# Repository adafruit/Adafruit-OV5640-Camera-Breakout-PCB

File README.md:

## Adafruit OV5640 Camera Breakout - 120 Degree Lens PCB

<a href="http://www.adafruit.com/products/5673"><br/>
Click here to purchase one from the Adafruit shop</a>

PCB files for the Adafruit OV5640 Camera Breakout - 120 Degree Lens. 

Format is EagleCAD schematic and board layout
* https://www.adafruit.com/product/5673

### Description

Hobby-level microcontrollers are finally getting big and powerful enough to start handling camera modules that historically would have required a full computer or FPGA to handle. The RP2040 and ESP32-Sx series of chips, for example, have enough pins to communicate with the 8-bit data output, DMA to quickly grab a frame, and the necessary RAM to buffer a raw snapshot. Now all we need is a nice camera module to make interfacing easy!

This Adafruit OV5640 Camera Breakout with 120 Degree Lens has a nice quality OV5640 camera with a 5 Megapixel sensor element, 120-degree wide angle lens, and all the support circuitry you need. We looked at existing camera modules and while this breakout board is backwards compatible, we made some improvements:

* Standard 2x9 header if you want it, but also a duplicated header strip 0.3" apart so you can plug it into a breadboard or perfboard 
* Selectable external or internal 24MHz "XCLK" clock generation - save one gpio pin, or just have a nice stable 24 MHz signal even if your microcontroller can't generate it for you.
* Heat-sinking camera area with exposed ground pad, with lots of vias for good thermal transfer. Helpful for when doing continuous encoding and reducing thermal image drift.
* Optional VMotor 3.3V power jumper on DATA1, for auto-focusing camera modules
* 3.3V power-good LED on back that can be disabled

### License

Adafruit invests time and resources providing this open source design, please support Adafruit and open-source hardware by purchasing products from [Adafruit](https://www.adafruit.com)!

Designed by Limor Fried/Ladyada for Adafruit Industries.

Creative Commons Attribution/Share-Alike, all text above must be included in any redistribution. 
See license.txt for additional details.

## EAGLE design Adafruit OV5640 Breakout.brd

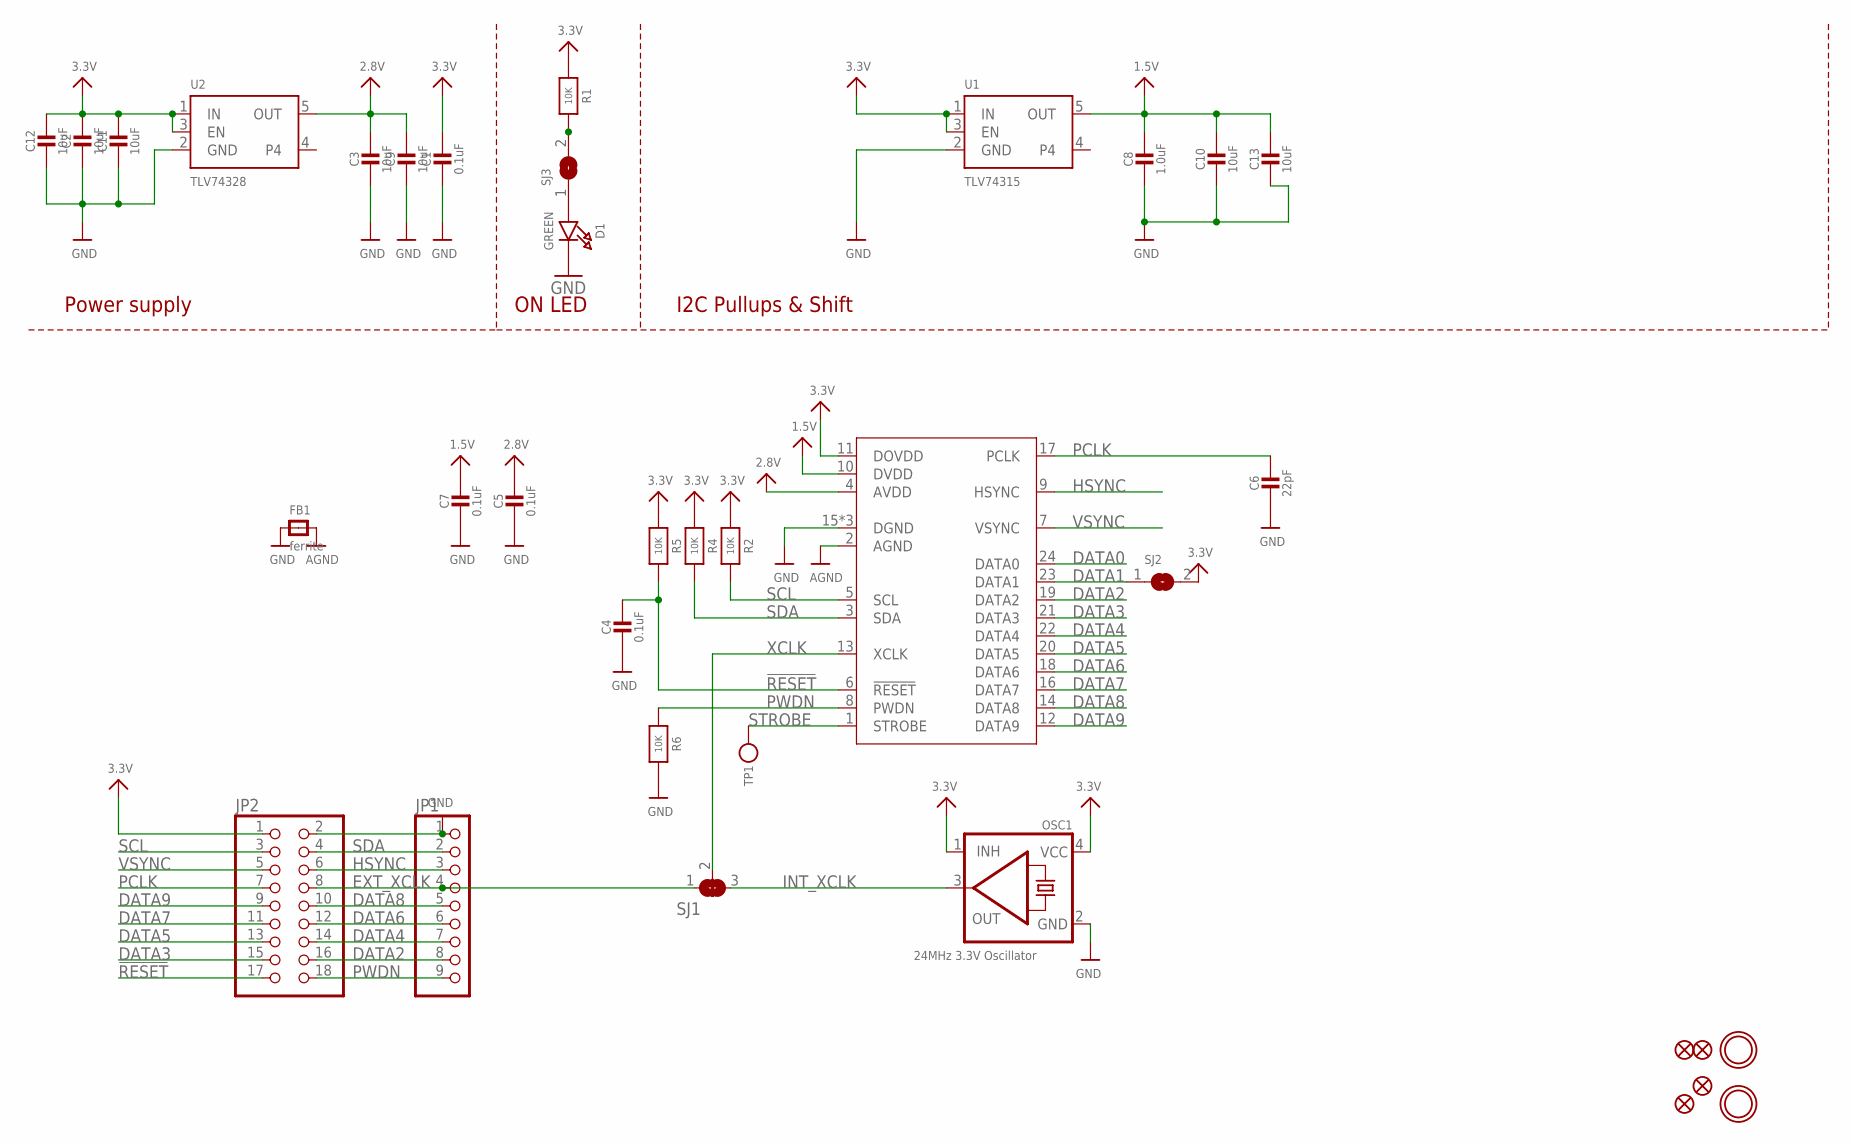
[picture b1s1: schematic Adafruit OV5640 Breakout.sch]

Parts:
C1, C4, C5, C7: 0.1uF; 0603-NO
C2, C3, C9, C10, C11, C12, C13: 10uF; 0805-NO
C6: 22pF; 0603-NO
C8: 1.0uF; 0603-NO
D1: GREEN; CHIPLED_0603_NOOUTLINE
FB1: ferrite; 0603-NO
FID1, FID2, FID3, FID4: FIDUCIAL_1MM
JP1: HEADER-1X970MIL; 1X09_ROUND_70
JP2: PINHD-2X9-BIG; 2X09-BIG
OSC1: 24MHz 3.3V Oscillator; OSC_3.2X2.5MM
R1, R2, R4, R5, R6: 10K; 0603-NO
SJ1: SOLDERJUMPER_2WAY; SOLDERJUMPER_2WAY_OPEN_NOPASTE
SJ2: SOLDERJUMPER; SOLDERJUMPER_ARROW_NOPASTE
SJ3: SOLDERJUMPERCLOSED; SOLDERJUMPER_CLOSEDWIRE
TP1: TESTPOINTROUND1.5MM; TESTPOINT_ROUND_1.5MM
U1: TLV74315; SOT23-5; JLC_ROTATION 0
U2: TLV74328; SOT23-5; JLC_ROTATION 0
U$1, U$17: MOUNTINGHOLE3.0THIN; MOUNTINGHOLE_3.0_PLATEDTHIN
X1: CAMERA_OV2640; OV2640FSL

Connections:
1.5V: C7.1, C8.1, C10.1, C13.1, U1.5 (OUT), X1.10 (DVDD)
2.8V: C3.1, C5.1, C9.1, U2.5 (OUT), X1.4 (AVDD)
3.3V: C1.1, C2.1, C11.1, C12.1, JP2.1, OSC1.1 (INH), OSC1.4 (VCC), R1.1, R2.1, R4.1, R5.1, SJ2.2, U1.1 (IN), U1.3 (EN), U2.1 (IN), U2.3 (EN), X1.11 (DOVDD)
!RESET: C4.1, JP2.17, R5.2, X1.6 (!RESET)
AGND: FB1.2, X1.2 (AGND)
DATA0: X1.24 (DATA0)
DATA1: SJ2.1, X1.23 (DATA1)
DATA2: JP1.8, JP2.16, X1.19 (DATA2)
DATA3: JP2.15, X1.21 (DATA3)
DATA4: JP1.7, JP2.14, X1.22 (DATA4)
DATA5: JP2.13, X1.20 (DATA5)
DATA6: JP1.6, JP2.12, X1.18 (DATA6)
DATA7: JP2.11, X1.16 (DATA7)
DATA8: JP1.5, JP2.10, X1.14 (DATA8)
DATA9: JP2.9, X1.12 (DATA9)
EXT_XCLK: JP1.4, JP2.8, SJ1.1
GND: C1.2, C2.2, C3.2, C4.2, C5.2, C6.2, C7.2, C8.2, C9.2, C10.2, C11.2, C12.2, C13.2, D1.C, FB1.1, JP1.1, JP2.2, OSC1.2 (GND), R6.2, U1.2 (GND), U2.2 (GND), X1.15 (DGND), X1.SPRT1 (DGND), X1.SPRT2 (DGND)
HSYNC: JP1.3, JP2.6, X1.9 (HSYNC)
INT_XCLK: OSC1.3 (OUT), SJ1.3
unnamed: R1.2, SJ3.2
unnamed: D1.A, SJ3.1
PCLK: C6.1, JP2.7, X1.17 (PCLK)
PWDN: JP1.9, JP2.18, R6.1, X1.8 (PWDN)
SCL: JP2.3, R2.2, X1.5 (SCL)
SDA: JP1.2, JP2.4, R4.2, X1.3 (SDA)
STROBE: TP1.P$1, X1.1 (STROBE)
VSYNC: JP2.5, X1.7 (VSYNC)
XCLK: SJ1.2, X1.13 (XCLK)

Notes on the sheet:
I2C Pullups & Shift
ON LED
Power supply

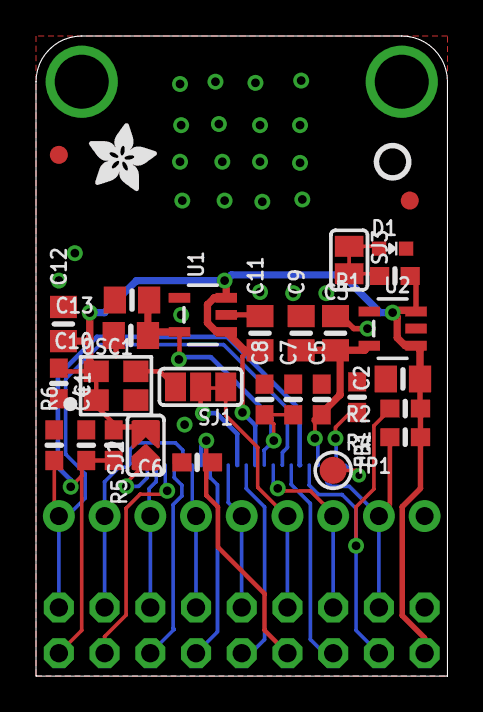
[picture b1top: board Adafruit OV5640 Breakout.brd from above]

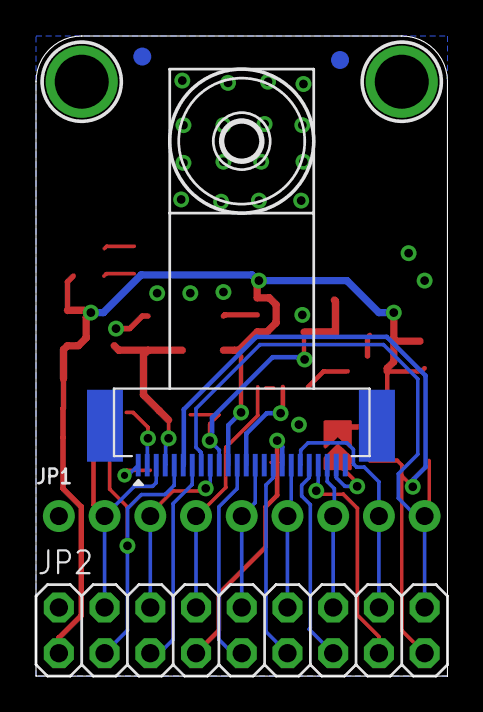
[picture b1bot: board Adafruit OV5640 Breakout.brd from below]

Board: 2 copper layers, 22.9 x 35.6 mm, 64 parts (27 on the bottom side), 27 nets.

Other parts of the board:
PLABEL0: PLABEL0
PLABEL1: PLABEL1
PLABEL2: PLABEL2
PLABEL3: PLABEL3
PLABEL4: PLABEL4
PLABEL5: PLABEL5
PLABEL6: PLABEL6
PLABEL7: PLABEL7
PLABEL8: PLABEL8
PLABEL9: PLABEL9
PLABEL10: PLABEL10
PLABEL11: PLABEL11
PLABEL12: PLABEL12
PLABEL13: PLABEL13
PLABEL14: PLABEL14
PLABEL15: PLABEL15
PLABEL16: PLABEL16
PLABEL17: PLABEL17
PLABEL18: PLABEL18
PLABEL19: PLABEL19
PLABEL20: PLABEL20
PLABEL21: PLABEL21
PLABEL22: PLABEL22
PLABEL23: PLABEL23
PLABEL24: PLABEL24
PLABEL25: PLABEL25
U$22: ADAFRUIT_3.5MM
U$25: PCBFEAT-REV-040

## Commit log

2023-02-08 adding cookiecutter output
2023-02-08 adding bullet points to markdown

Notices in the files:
parts and their libraries:
microbuilder: This work is placed in the public domain, and may be freely used for commercial and non-commercial work with the following conditions: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
